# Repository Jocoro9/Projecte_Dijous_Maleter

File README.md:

View this project on [CADLAB.io](https://cadlab.io/project/29047). 

# Projecte_Dijous_Maleter

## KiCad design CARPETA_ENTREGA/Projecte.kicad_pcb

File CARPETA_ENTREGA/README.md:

View this project on [CADLAB.io](https://cadlab.io/project/29047). 

Aquest projecte conté els elements necessaris per la fabricació de una PCB que gestiona un maletero.

# Projecte_Dijous_Maleter

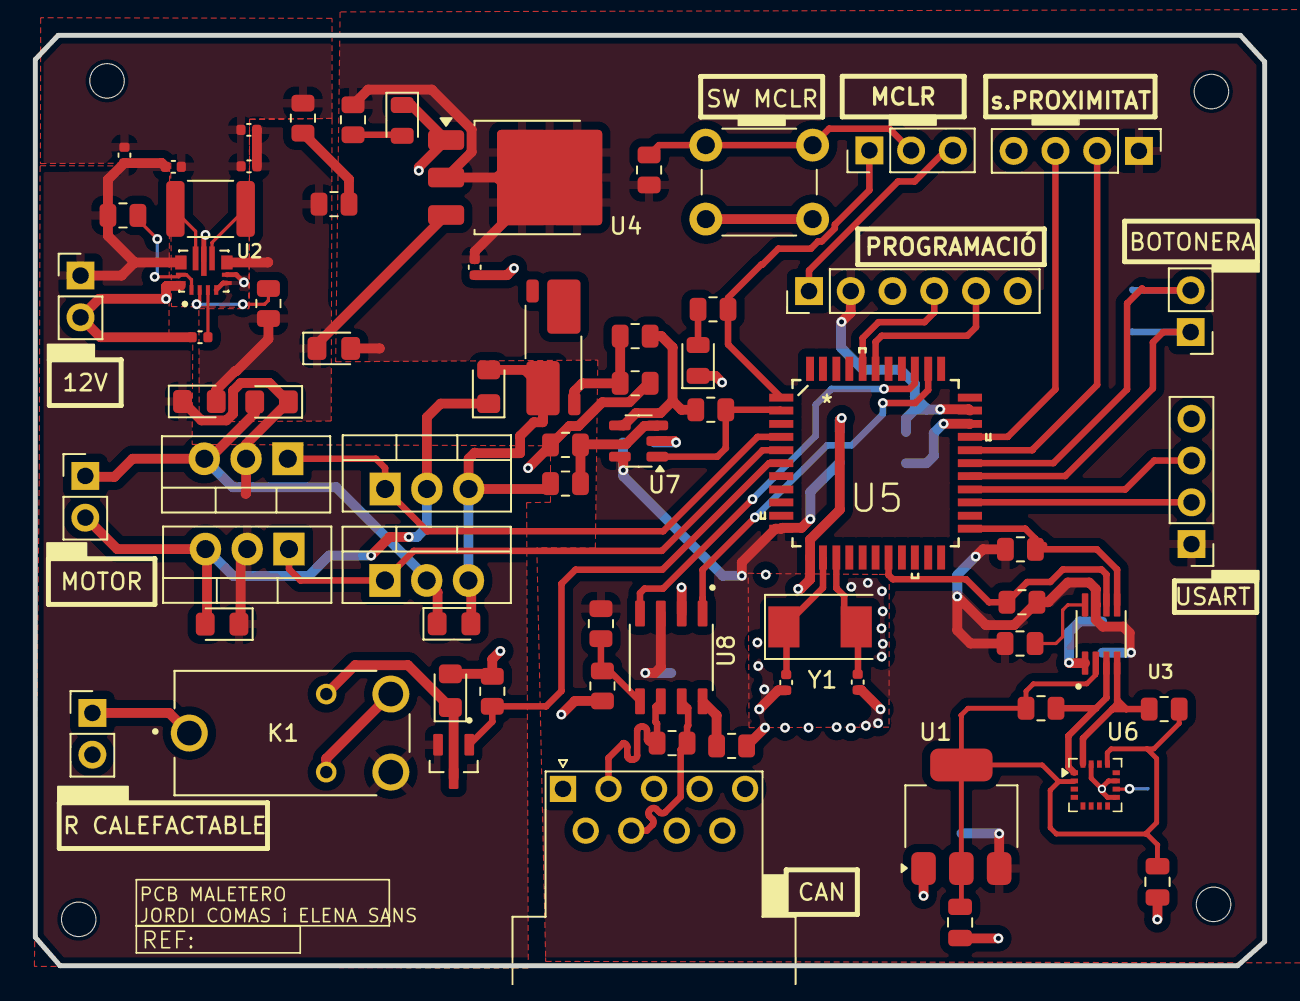
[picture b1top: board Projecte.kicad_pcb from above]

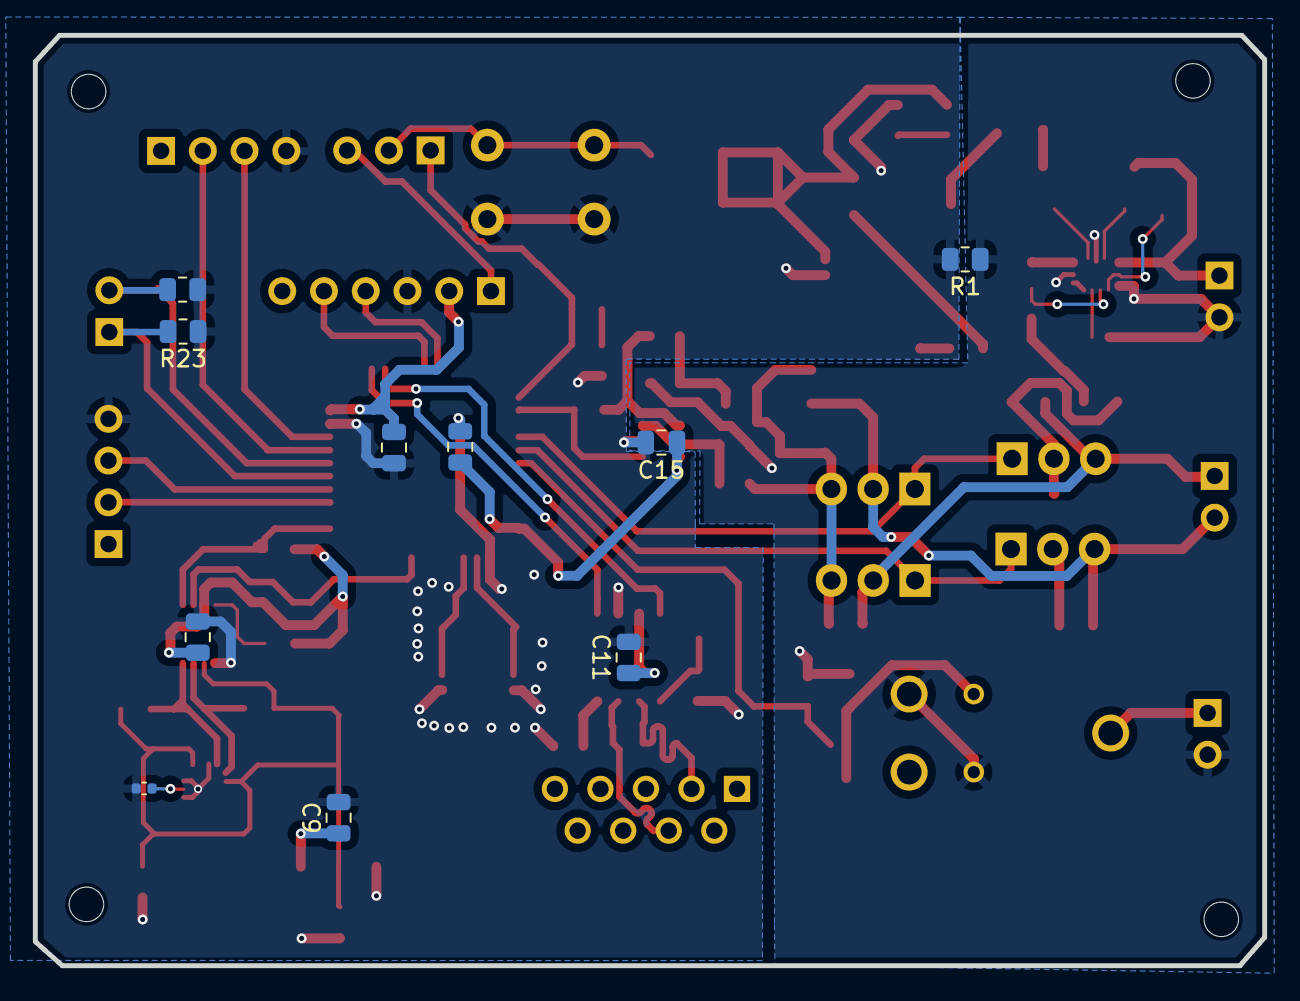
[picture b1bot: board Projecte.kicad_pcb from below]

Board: 2 copper layers, 74.8 x 56.6 mm, 78 parts (10 on the bottom side), 51 nets.

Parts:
12V: Conn_01x02_Pin; PinHeader_1x02_P2.54mm_Vertical
BOTONERA: Conn_01x02_Pin; PinHeader_1x02_P2.54mm_Vertical
C2: 22u; C_0805_2012Metric
C3, C5: 15p; C_0402_1005Metric
C4, C6, C7, C10, C11, C12, C13#2: 10u; C_0402_1005Metric
C8, C9, C11#2, C13, C15, C16: 100n; C_0805_2012Metric
C14: 1u; C_0805_2012Metric
CAN: DE9_Pins; DSUB-9_Pins_Horizontal_P2.77x2.54mm_EdgePinOffset9.40mm
D1: D; D_0805_2012Metric_Pad1.15x1.40mm_HandSolder
D2: DPM-1; D_0805_2012Metric_Pad1.15x1.40mm_HandSolder
DPA1, DPA2: D; D_0805_2012Metric_Pad1.15x1.40mm_HandSolder
DPM+1, DPM+2: D; D_0805_2012Metric_Pad1.15x1.40mm_HandSolder
DPM-1: D; D_0805_2012Metric_Pad1.15x1.40mm_HandSolder
DR1, DR2: LED; LED_0805_2012Metric
K1: A161CS12VDC.64; RELAY_A161CS12VDC.64
L1: 1,5u; L_1812_4532Metric
MCLR: Conn_01x03; PinHeader_1x03_P2.54mm_Vertical
MOTOR: Conn_01x02_Pin; PinHeader_1x02_P2.54mm_Vertical
PROGRAMACIÓ: Conn_01x06_Pin; PinHeader_1x06_P2.54mm_Vertical
Q1: IRLML2502; SOT95P237X112-3N
Q2, Q3, Q4, Q5: IRLZ34N; TO-220-3_Vertical
R1: 0; R_0805_2012Metric
R2: R; R_0805_2012Metric
R3, R5, R7, R12: 2.7k; R_0805_2012Metric
R4, R8, R9, R11, R13, R14, R15, R16, R17, R19, R21: 1k; R_0805_2012Metric
R6, R23, R24: 200k; R_0805_2012Metric
R10: 680; R_0805_2012Metric
R18, R20: 2k; R_0805_2012Metric
R22: 120R; R_0805_2012Metric
R CALEFACTABLE: Conn_01x02_Pin; PinHeader_1x02_P2.54mm_Vertical
RMCLR1: 1k; R_0805_2012Metric
R_shunt1: 0.005R; R_Shunt_Vishay_WSK2512_6332Metric_T2.21mm
SW MCLR: SW_Push; SW_PUSH_6mm
U1: AMS1117-3.3; SOT-223-3_TabPin2
U2: TPS63070RNMR
U3: PCA9306; PCA
U4: LM1117DT-5.0; TO-252-3_TabPin2
U5: PIC18F448-IP; PIC258SMD
U6: MMC5883MA; LGA-16_3x3mm_P0.5mm
U7: OPA336Nx; SOT-23-5
U8: MCP2551-I-P; SOIC127P599X175-8N
USART: Conn_01x04_Pin; PinHeader_1x04_P2.54mm_Vertical
Y1: Crystal; Crystal_SMD_0603-2Pin_6.0x3.5mm
s.PROXIMITAT: Conn_01x04_Pin; PinHeader_1x04_P2.54mm_Vertical

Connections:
+12V: 12V.1, C4.1, C7.1, DPA1.1 (K), DPM+1.1 (K), DPM-1.1 (K), K1.NO, Q1.2 (D), Q2.2 (D), Q4.2 (D), R4.2, U2.12_13 (VIN)
/Baixar: Q3.1 (G), Q4.1 (G), U5.5 (RA3/AN3/Vref+)
/Boto_Motor: BOTONERA.1, R23.2, U5.27 (P1A/ECCP1/PSP4/RD4)
/Boto_R: BOTONERA.2, R24.2, U5.28 (P1B/PSP5/RD5)
/Canh: CAN.7, R22.2, U8.7 (CANH)
/Canl: CAN.2, R22.1, U8.6 (CANL)
/L1: L1.1, U2.11 (L1)
/L2: L1.2, U2.9 (L2)
/M+: DPM+1.2 (A), DPM+2.1 (K), MOTOR.1, Q2.3 (S), Q3.2 (D)
/M-: D2.1 (K), DPM-1.2 (A), MOTOR.2, Q4.3 (S), Q5.2 (D)
/MCLR: MCLR.1, R2.2, U5.1 (~MCLR/VPP)
/Man_CLR: MCLR.2, RMCLR1.1, SW MCLR.1
/Osc1: C3.1, U5.13 (OSC1/CLKIN), Y1.1
/Osc2: C5.1, U5.14 (RA6/OSC2/CLKO), Y1.2
/PGC: PROGRAMACIÓ.5, U5.39 (RB6/PGC)
/PGD: PROGRAMACIÓ.4, U5.40 (RB7/PGD)
/PG_: R11.1, U2.2 (PG)
/PS: R4.1, U2.1 (PS/SYNC), U2.14 (EN)
/Pujar: Q2.1 (G), Q5.1 (G), U5.4 (RA2/AN2/Vref-)
/R_on: Q1.1 (G), R13.1, U5.6 (RA4/TOCKI)
/RsU4: R17.2, U8.8 (Rs)
/Rx: U5.36 (RB3/CANRX), U8.4 (RXD)
/SCL: R7.1, U3.6 (SCL2), U5.18 (SCK/SCL/RC3)
/SCL_S: R5.1, U3.3 (SCL1), U6.1 (SCL)
/SDA: R12.1, U3.5 (SDA2), U5.23 (SDI/SDA/RC4)
/SDA_S: R3.1, U3.4 (SDA1), U6.16 (SDA)
/S_entrada: U5.29 (P1C/PSP6/RD6), s.PROXIMITAT.2
/S_sortida: U5.30 (P1D/PSP7/RD7), s.PROXIMITAT.3
/Tx: U5.35 (RB2/INT2/CANTX), U8.1 (TXD)
/V+: R15.1, R18.2, U7.3 (+)
/V-s: R16.1, R20.1, U7.4 (-)
/VR_Calef_+: K1.COM, R CALEFACTABLE.1
/V_LED_ON: DR2.2 (A), R10.1
/V_LED_XIP: DR1.2 (A), R2.1
/Vadj: R8.1, R9.2
/Vaux: C6.1, U2.3 (VAUX)
/Vcc_3.3V: C2.1, C14.1, R3.2, R5.2, U1.2 (VO), U3.2 (VREF1), U6.2 (VDD), U6.13 (VDDIO)
/Vouta1: C10.1, C11.1, DPA1.2 (A), DPA2.1 (K), R8.2, R11.2, U2.7_8 (VOUT), U4.3 (VI)
/Vpp: MCLR.3, PROGRAMACIÓ.1
/Vref: R19.2, R21.1, U8.5 (Vref)
/Vrele: D1.1 (K), K1.A1, Q1.3 (S)
/Vs.7: R14.1, R16.2, R_shunt1.2
/corrent: R20.2, U5.2 (RA0/AN0/CVref), U7.1
/shunt: D2.2 (A), DPM+2.2 (A), Q3.3 (S), Q5.3 (S), R15.2, R_shunt1.1
/usart_rx: U5.26 (RX/DT/RC7), USART.3
/usart_tx: U5.25 (TX/CK/RC6), USART.2
GND: C2.2, C3.2, C5.2, C8.2, C9.2, C11#2.2, C12.2, C13.2, C13#2.2, C14.2, C15.2, C16.2, DR1.1 (K), DR2.1 (K), PROGRAMACIÓ.3, R1.2, R17.1, R21.2, R23.1, R24.1, SW MCLR.2, U1.1 (GND), U3.1 (GND), U4.1 (GND), U5.12 (VSS), U5.31 (VSS), U6.9 (GND), U6.11 (GND), U6.15 (INT), U7.2 (V-), U8.2 (VSS), USART.4, s.PROXIMITAT.4
GNDPWR: 12V.2, C4.2, C6.2, C7.2, C10.2, C11.2, D1.2 (A), K1.A2, K1.NC, R1.1, R9.1, R13.2, R14.2, R18.1, R CALEFACTABLE.2, U2.4 (GND), U2.5 (FB), U2.6 (FB2), U2.10 (PGND), U2.15 (VSEL)
unnamed: R6.2, U3.8 (EN)
unnamed: C13#2.1, U6.10 (CAP)
VCC: C8.1, C9.1, C11#2.1, C12.1, C13.1, C15.1, C16.1, DPA2.2 (A), PROGRAMACIÓ.2, R6.1, R7.2, R10.2, R12.2, R19.1, RMCLR1.2, U1.3 (VI), U3.7 (VREF2), U4.2 (VO), U5.11 (VDD), U5.32 (VDD), U7.5 (V+), U8.3 (VDD), USART.1, s.PROXIMITAT.1

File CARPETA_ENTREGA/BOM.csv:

"Reference","Qty","Value","DNP","Exclude from BOM","Exclude from Board","Footprint","Datasheet"
"12V1,BOTONERA1,MOTOR1,R_CALEFACTABLE1","4","Conn_01x02_Pin","","","","Connector_PinHeader_2.54mm:PinHeader_1x02_P2.54mm_Vertical","~"
"C1,C4,C6,C7,C10,C11,C12,C13","8","10u","","","","Capacitor_SMD:C_0402_1005Metric","~"
"C2","1","22u","","","","Capacitor_SMD:C_0805_2012Metric","~"
"C3,C5","2","15p","","","","Capacitor_SMD:C_0402_1005Metric","~"
"C8,C9,C15,C16","4","100n","","","","Capacitor_SMD:C_0805_2012Metric","~"
"C14","1","1u","","","","Capacitor_SMD:C_0805_2012Metric","~"
"CAN1","1","DE9_Pins","","","","Connector_Dsub:DSUB-9_Pins_Horizontal_P2.77x2.54mm_EdgePinOffset9.40mm","~"
"D1,DPA1,DPA2,DPM+1,DPM+2,DPM-1","6","D","","","","Diode_SMD:D_0805_2012Metric_Pad1.15x1.40mm_HandSolder","~"
"D2","1","DPM-1","","","","Diode_SMD:D_0805_2012Metric_Pad1.15x1.40mm_HandSolder","~"
"DR1,DR2","2","LED","","","","LED_SMD:LED_0805_2012Metric","~"
"J_MCLR1","1","Conn_01x03","","","","Connector_PinHeader_2.54mm:PinHeader_1x03_P2.54mm_Vertical","~"
"K1","1","A161CS12VDC.64","","","","Library:RELAY_A161CS12VDC.64",""
"L1","1","1,5u","","","","Inductor_SMD:L_1812_4532Metric","~"
"PROGRAMACI?","1","Conn_01x06_Pin","","","","Connector_PinHeader_2.54mm:PinHeader_1x06_P2.54mm_Vertical","~"
"Q1","1","IRLML2502","","","","Library:SOT95P237X112-3N","http://www.infineon.com/dgdl/irlz34npbf.pdf?fileId=5546d4625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"
"Q2,Q3,Q4,Q5","4","IRLZ34N","","","","Package_TO_SOT_THT:TO-220-3_Vertical","http://www.infineon.com/dgdl/irlz34npbf.pdf?fileId=5546d4625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"
"R1","1","0","","","","Resistor_SMD:R_0805_2012Metric","~"
"R2","1","R","","","","Resistor_SMD:R_0805_2012Metric","~"
"R3,R5,R7,R12","4","2.7k","","","","Resistor_SMD:R_0805_2012Metric","~"
"R4,R8,R9,R11,R13,R14,R15,R16,R17,R19,R21,RMCLR1","12","1k","","","","Resistor_SMD:R_0805_2012Metric","~"
"R6,R23,R24","3","200k","","","","Resistor_SMD:R_0805_2012Metric","~"
"R10","1","680","","","","Resistor_SMD:R_0805_2012Metric","~"
"R18,R20","2","2k","","","","Resistor_SMD:R_0805_2012Metric","~"
"R22","1","120R","","","","Resistor_SMD:R_0805_2012Metric","~"
"R_shunt1","1","0.005R","","","","Resistor_SMD:R_Shunt_Vishay_WSK2512_6332Metric_T2.21mm","~"
"s.PROXIMITAT1,USART1","2","Conn_01x04_Pin","","","","Connector_PinHeader_2.54mm:PinHeader_1x04_P2.54mm_Vertical","~"
"SW_MCLR1","1","SW_Push","","","","Button_Switch_THT:SW_PUSH_6mm","~"
"U1","1","AMS1117-3.3","","","","Package_TO_SOT_SMD:SOT-223-3_TabPin2","http://www.advanced-monolithic.com/pdf/ds1117.pdf"
"U2","1","TPS63070RNMR","","","","Library:TPS63070RNMR",""
"U3","1","PCA9306","","","","Library:PCA","http://www.ti.com/lit/ds/symlink/pca9306.pdf"
"U4","1","LM1117DT-5.0","","","","Package_TO_SOT_SMD:TO-252-3_TabPin2","http://www.ti.com/lit/ds/symlink/lm1117.pdf"
"U5","1","PIC18F448-IP","","","","Library:PIC258SMD","http://ww1.microchip.com/downloads/en/DeviceDoc/41159e.pdf"
"U6","1","MMC5883MA","","","","Package_LGA:LGA-16_3x3mm_P0.5mm","http://www.memsic.com/userfiles/files/DataSheets/Magnetic-Se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"
"U7","1","OPA336Nx","","","","Package_TO_SOT_SMD:SOT-23-5","https://www.ti.com/lit/ds/symlink/opa2336.pdf"
"U8","1","MCP2551-I-P","","","","Library:SOIC127P599X175-8N","http://ww1.microchip.com/downloads/en/devicedoc/21667d.pdf"
"Y1","1","Crystal","","","","Crystal:Crystal_SMD_0603-2Pin_6.0x3.5mm","~"

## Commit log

2025-03-20 patata
2025-03-26 Actualització_Esquematic
    En el esquematic s'ha afegit el clock, el pont H fet amb mosfets, alguns conectors i el LDO
2025-03-26 Otra
    He afeguit el transciver, i estic fent el programming del xip, no tinc molt clar si esta bé pero working on it si vols fer tu els sensors de lokos.
2025-03-26 V2
    S'ha afeguit el relé, s'han conectat els senyals de control al micro, s'han corregit errors i s'ha dinamitzat el esquematic.
2025-03-27 Simulacions
    --
2025-03-27 Act_v3
2025-03-27 Backlink to CADLAB.io has been added.
2025-03-27 Sch_Post_Show
2025-03-30 Primer_Layout
    S'han aplicat le footprints als components i s'ha fet un primer placement a la placa de manera que els components de una mateixa etapa quedin junts.
2025-03-31 jsdf
2025-04-01 fix git
2025-04-02 02/04
2025-04-03 Layout
2025-04-04 Canvis_Layout
2025-04-08 Layout_V2
2025-04-08 Push
2025-04-21 Layout_Final
2025-04-24 push_final
